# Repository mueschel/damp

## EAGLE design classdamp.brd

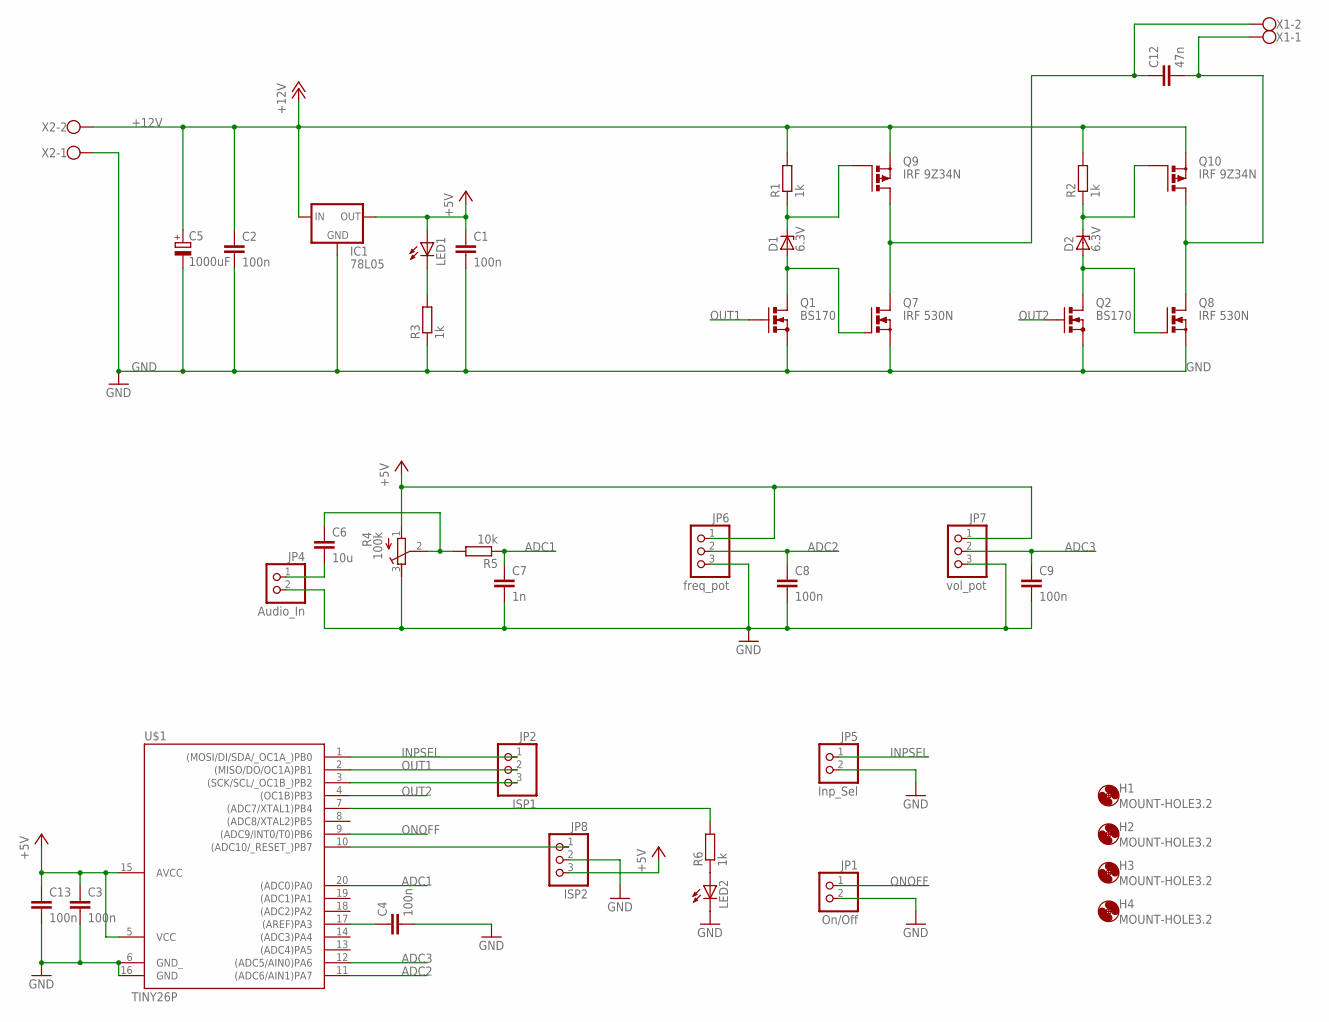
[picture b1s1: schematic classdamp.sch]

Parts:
C1, C2, C3, C4, C8, C9, C13: 100n; C0805K
C5: 1000uF; E5-8,5
C6: 10u; C0805K
C7: 1n; C0805K
C12: 47n; C5B3.5
D1, D2: 6.3V; ZDIO-5
H1, H2, H3, H4: MOUNT-HOLE3.2; 3,2
IC1: 78L05; 78LXX
JP1: On/Off; 1X02
JP2: ISP1; 1X03
JP4: Audio_In; 1X02
JP5: Inp_Sel; 1X02
JP6: freq_pot; 1X03
JP7: vol_pot; 1X03
JP8: ISP2; 1X03
LED1, LED2: LEDSML0805; SML0805
Q1, Q2: BS170; SOT54E
Q7, Q8: IRF 530N; TO220BV
Q9, Q10: IRF 9Z34N; TO220BV
R1, R2, R3, R6: 1k; R0805
R4: 100k; RTRIM64W
R5: 10k; R0805
U$1: TINY26P; DIL20
X1, X2: W237-102

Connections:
+5V: C1.1, C3.1, C13.1, IC1.OUT, JP6.1, JP7.1, JP8.3, LED1.A, R4.1 (E), U$1.5 (VCC), U$1.15 (AVCC)
+12V: C2.1, C5.+, IC1.IN, Q9.S, Q10.S, R1.2, R2.2, X2.2
ADC1: C7.1, R5.1, U$1.20 ((ADC0)PA0)
ADC2: C8.1, JP6.2, U$1.11 ((ADC6/AIN1)PA7)
ADC3: C9.1, JP7.2, U$1.12 ((ADC5/AIN0)PA6)
GND: C1.2, C2.2, C3.2, C4.2, C5.-, C7.2, C8.2, C9.2, C13.2, IC1.GND, JP1.2, JP4.2, JP5.2, JP6.3, JP7.3, JP8.2, LED2.C, Q1.S, Q2.S, Q7.S, Q8.S, R3.1, R4.3 (A), U$1.6 (GND_), U$1.16 (GND), X2.1
INPSEL: JP2.1, JP5.1, U$1.1 ((MOSI/DI/SDA/_OC1A_)PB0)
unnamed: LED1.C, R3.2
unnamed: C4.1, U$1.17 ((AREF)PA3)
unnamed: LED2.A, R6.1
unnamed: D1.A, Q1.D, Q7.G
unnamed: D2.A, Q2.D, Q8.G
unnamed: D1.C, Q9.G, R1.1
unnamed: D2.C, Q10.G, R2.1
unnamed: C6.2, JP4.1
unnamed: JP2.3, U$1.3 ((SCK/SCL/_OC1B_)PB2)
unnamed: C6.1, R4.2 (S), R5.2
unnamed: C12.1, Q7.D, Q9.D, X1.2
unnamed: JP8.1, U$1.10 ((ADC10/_RESET_)PB7)
unnamed: C12.2, Q8.D, Q10.D, X1.1
unnamed: R6.2, U$1.7 ((ADC7/XTAL1)PB4)
ONOFF: JP1.1, U$1.9 ((ADC9/INT0/T0)PB6)
OUT1: JP2.2, Q1.G, U$1.2 ((MISO/DO/OC1A)PB1)
OUT2: Q2.G, U$1.4 ((OC1B)PB3)

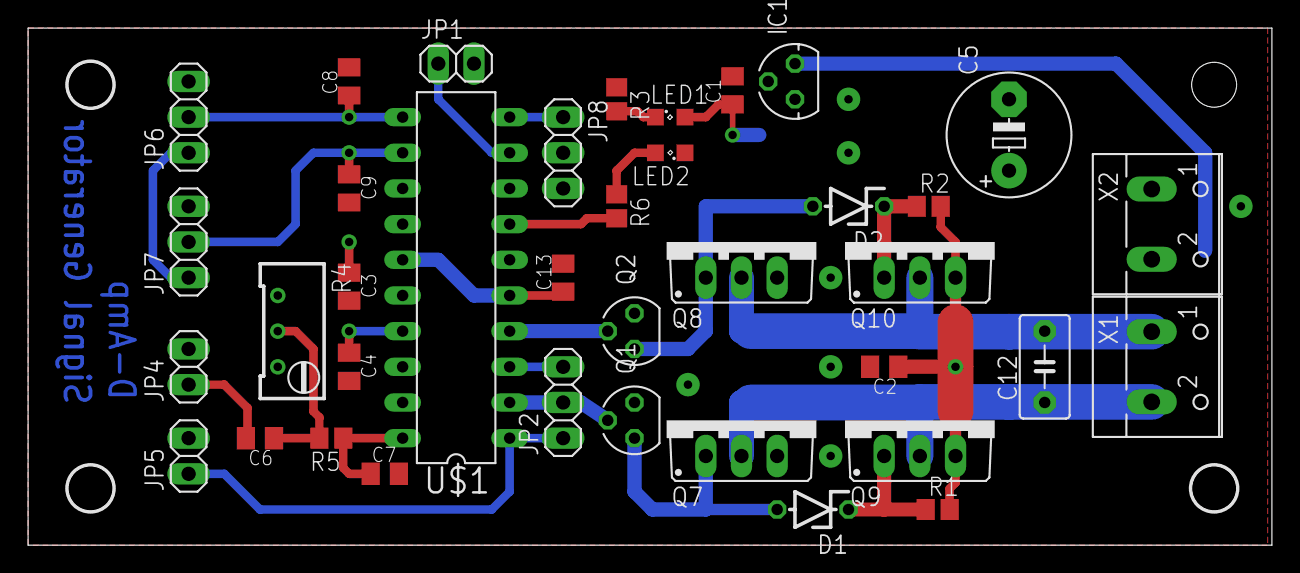
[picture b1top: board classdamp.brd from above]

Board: 2 copper layers, 88.6 x 36.8 mm, 42 parts (1 on the bottom side), 24 nets.

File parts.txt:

Partlist

Exported from classdamp.sch at 4/29/13 9:50 AM

EAGLE Version 6.4.0 Copyright (c) 1988-2013 CadSoft

Assembly variant: 

Part     Value          Device             Package  Library                 Sheet

C1       100n           C-EUC0805K         C0805K   resistor                1
C2       100n           C-EUC0805K         C0805K   resistor                1
C3       100n           C-EUC0805K         C0805K   resistor                1
C4       100n           C-EUC0805K         C0805K   resistor                1
C5       1000uF         CPOL-EUE5-8.5      E5-8,5   resistor                1
C6       10uF           CPOL-EUE1.8-4      E1,8-4   resistor                1
C7       1n             C-EUC0805K         C0805K   resistor                1
C8       100n           C-EUC0805K         C0805K   resistor                1
C9       100n           C-EUC0805K         C0805K   resistor                1
C12      47n            C5/3.5             C5B3.5   capacitor-wima          1
C13      100n           C-EUC0805K         C0805K   resistor                1
D1       6.3V           ZENER-DIODEZD-12.5 ZDIO12.5 diode                   1
D2       6.3V           ZENER-DIODEZD-12.5 ZDIO12.5 diode                   1
IC1      78L05          78LXX              78LXX    v-reg                   1
JP1      On/Off         PINHD-1X2          1X02     pinhead                 1
JP2      ISP1           PINHD-1X3          1X03     pinhead                 1
JP4      Audio_In       PINHD-1X2          1X02     pinhead                 1
JP5      Inp_Sel        PINHD-1X2          1X02     pinhead                 1
JP6      freq_pot       PINHD-1X3          1X03     pinhead                 1
JP7      vol_pot        PINHD-1X3          1X03     pinhead                 1
JP8      ISP2           PINHD-1X3          1X03     pinhead                 1
LED1                    LED5MM             LED5MM   led                     1
Q1       BS170          BS170              SOT54E   transistor-small-signal 1
Q2       BS170          BS170              SOT54E   transistor-small-signal 1
Q7       IRF 530N       PMOSFET_NTO220BV   TO220BV  transistor-power        1
Q8       IRF 530N       PMOSFET_NTO220BV   TO220BV  transistor-power        1
Q9       IRF 9Z34N      PMOSFET_PTO220BV   TO220BV  transistor-power        1
Q10      IRF 9Z34N      PMOSFET_PTO220BV   TO220BV  transistor-power        1
R1       1k             R-EU_R0805         R0805    resistor                1
R2       1k             R-EU_R0805         R0805    resistor                1
R3       1k             R-EU_R0805         R0805    resistor                1
R4       100k           R-TRIMM64W         RTRIM64W resistor                1
R5       10k            R-EU_R0805         R0805    resistor                1
U$1      TINY26P        TINY26P            DIL20    avr-7                   1
X1                      W237-102           W237-102 con-wago-500            1
X2                      W237-102           W237-102 con-wago-500            1

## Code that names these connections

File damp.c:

#define F_CPU 16000000UL

#include <avr/interrupt.h>
#include <util/delay.h>
#include <avr/sleep.h>
#include <stdint.h>

//PB0  input select
//PB1  OC1A Output1
//PB2
//PB3  OC1B Output2
//PB4  LED
//PB6  input onoff
//PB7  reset

//PA0 ADC0  Audio In
//PA6 ADC5  volume
//PA7 ADC6  frequency

//CKSEL fuses should be 0b0001 - PLL as source

#define FREQMODE 1
#define AUDIOMODE 0
#define DACP OCR1A
#define DACN OCR1B
#define DACT TC1H

volatile uint8_t mode_select = AUDIOMODE; //1: frequency generator, 0: external sound input

volatile uint8_t amplitude = 1;  //amplitude
volatile uint16_t real_value_pos = 512;
volatile uint16_t real_value_neg = 512;

#define ADMUX_AUDIO         (1<<REFS0) | (1<<REFS1) | (0<<ADLAR) | 0   //input 0, reference internal 2.56V with capacitor
#define ADCSRA_AUDIO        (1<<ADEN) | (1<<ADSC) | (1<<ADATE) | (1<<ADIE) | (5<<ADPS0)
#define TCCR0B_AUDIO        0

#define ADMUX_FREQ          (0<<REFS0) | (0<<REFS1) | (0<<ADLAR) | 5 // PB3, AVcc, 8 bit, 5V, left aligned
#define ADCSRA_FREQ         (1<<ADEN) | (1<<ADSC) | (1<<ADATE) | (1<<ADIE) | (7<<ADPS0) // CPU/128 sampling rate (9.6kHz);
#define TCCR0B_FREQ         (3<<CS00)


__attribute__((naked)) int main(void)
{
    _delay_ms(500);

    //Port A is ADC only
    DIDR0  = 0xFF; //(1<<ADC6D) | (1<<ADC5D) | (1<<ADC0D); //disable digital input on ADC pins

	// ADC
	ADMUX  = ADMUX_AUDIO ;
	ADCSRA = ADCSRA_AUDIO; 
    ADCSRB = (1<<REFS2);

	// Timer0: Signal generation (CTC /256)
	OCR0A = 10; //interval to generate interrupt
    TCCR0A = (1<<0); //CTC mode  0: CTC0
    TCCR0B = TCCR0B_AUDIO;
    TIMSK |= (1<<OCIE0A); //interrupt on compare match / counter reset

    //Timer1: PWM
    TCCR1A = (1<<COM1A1) | (1<<COM1A0) | (1<<COM1B1) | (1<<COM1B0) | (0<<PWM1A) | (0<<PWM1B) | (1<<FOC1A) | (1<<FOC1B);
    TCCR1A = (1<<COM1A1) | (1<<COM1A0) | (1<<COM1B1) | (1<<COM1B0) | (1<<PWM1A) | (1<<PWM1B) | (0<<FOC1A) | (0<<FOC1B);
    TCCR1B = (0<<7) | (2<<CS10); //  CLK/1  -> 64MHz/1/1024 = 62kHz
    TCCR1C |= 0b11110000;
    TCCR1D = 0;
    //TCCR1E = 0x0a;
    TC1H   = 0x3;  //set overflow for timer to 0x3ff
    OCR1C  = 0xFF;
    TC1H   = 0;
    //OCR1A  = 0x0F;
    //OCR1B  = 0x0F;
    //TCNT1  = 0;
    PLLCSR = (1<<PCKE) | (1<<PLLE);
    TIMSK |= (1<<TOIE1);

	// Configure ports
	DDRB  = 0b00011010;
	PORTB = 0b11100001;

	sei();
	while(1) {
		_delay_us(100);
        
        if(mode_select != ((~PINB) & 1) ) {
            if(mode_select == AUDIOMODE) {  //change to generator
                mode_select = FREQMODE;
                TCCR0B = TCCR0B_FREQ;
	            ADMUX  = ADMUX_FREQ;
	            ADCSRA = ADCSRA_FREQ;
                }
            else {                  //change to Audio
                mode_select = AUDIOMODE;
                TCCR0B = TCCR0B_AUDIO;
	            ADMUX  = ADMUX_AUDIO;
	            ADCSRA = ADCSRA_AUDIO;
                }
            }
	    }
    }

//mode 1: switch between ADC 5 (vol) and 6 (freq), set frequency and amplitude registers, two reads per input
//mode 0: copy ADC value to real_value for PWM
ISR(ADC_vect) {
    static uint16_t period = 160;
	static uint8_t channel = 5;
	static uint8_t valid = 0; //accept only second read from each input.
	if(mode_select == FREQMODE) { // read 
		if(valid == 0) {
			valid = 1;
		} else {		
            sei();
			valid = 0;
			if (channel==6) {
    			ADMUX = (ADMUX & 0xF0) | 5;
				period -= period/4;
				period += ADC;
				if (period < 240) period = 240;  //upper limit to prevent too high interrupt load
				OCR0A = period/16;
				channel = 5;
			} else {
    			ADMUX = (ADMUX & 0xF0) | 6;
				amplitude = ADC >> 2;
				channel = 6;
	    		}		
		    }	
	    }		
    else {
        uint16_t real_value;
        real_value     = ADC;
	    real_value_pos = real_value;
	    real_value_neg = 1023 - real_value;

        }
		
}	

//called at F_CPU/64*period, run only every second time.
//10<period<255 --> 3.8 - 97 Hz
ISR(TIMER0_COMPA_vect) {
	sei();
    static uint8_t time = 0;
	static int8_t direction = 1;  //ramp up or down
    static int8_t value = 0;
    static uint8_t cur_amplitude = 0;
    static int16_t tmp_value = 0;
    
    if(++time & 1)
        return;

	//real_value = ((int16_t)value * cur_amplitude) / 8;
    if (value == 0) {
        tmp_value = 0; //reset to correct 0 value
        cur_amplitude = amplitude;
        }
    else {
        if (direction == 1)
            tmp_value = tmp_value + cur_amplitude;
        else
            tmp_value = tmp_value - cur_amplitude;
        }           

	if(value <= -63 || value >= 63)
    	direction = -direction;
	value = value + direction;

    uint16_t real_value = 1024 + tmp_value /16;
    uint16_t val1 = real_value >> 1;
    uint16_t val2 = 0;// real_value & 1;
    //if(val1 > 1023)
    //    val1 = 1023;
    //if(val1 < 0)
    //    val1 = 0;
    real_value_pos = val1 + val2;
    real_value_neg = 1023 - val1;
}

	

ISR(TIMER1_OVF_vect) {
    uint16_t pos;
    uint16_t neg;

    pos = real_value_pos;
    neg = real_value_neg;

    DACT = (pos >> 8);
	DACP = pos;

    DACT = (neg >> 8);
	DACN = neg;
}    

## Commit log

2013-04-27 First working version with signal generator.
2013-04-27 Warenkorb hinzugefügt.
2013-04-27 added original schematics & tested layout
2013-04-27 added new schematics
2013-04-27 size 37x89 -> 5 pieces on 200x90 PCB
2013-04-27 Changed text size, DRU passed.
2013-04-28 Just few small things...
2013-04-28 Bemaßung
2013-04-28 Adjusting...
2013-04-28 R/C durch SMD ersetzt - bessere GND-Flächen
2013-04-28 few details
2013-04-29 added partlist
2013-04-29 updated reichelt order
2013-04-29 few changes
2013-04-29 kind of a change
2013-05-05 Nothing important
2013-05-05 removed top layer for production
2013-05-05 adjusted width
2013-05-05 wrong layer...
2013-05-06 changed to dual-layer design
2013-05-06 updated partlist
2013-05-19 changed to tiny861
2013-05-20 added audio function. switch via on/off
2013-05-21 latest version
2013-05-21 performance tuning - hope that works
2013-05-21 latest changes
2013-05-23 latest version, added hex.
